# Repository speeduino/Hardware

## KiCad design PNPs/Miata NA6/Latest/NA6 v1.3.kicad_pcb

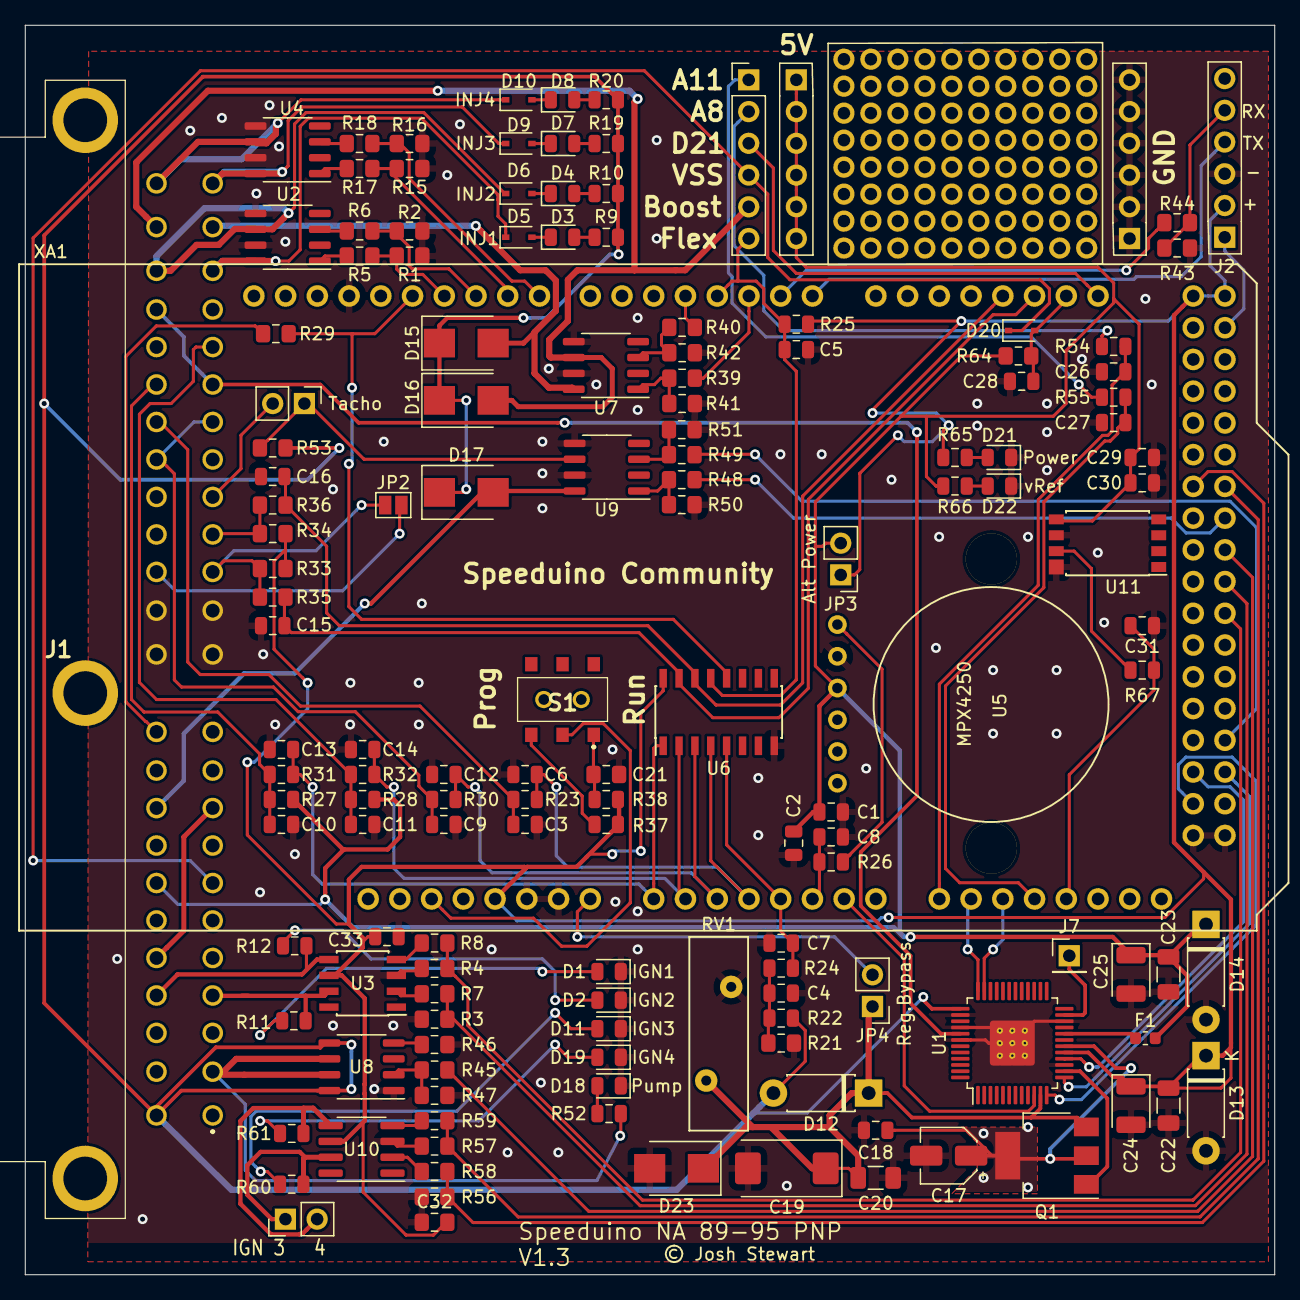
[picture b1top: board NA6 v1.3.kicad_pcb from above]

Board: 2 copper layers, 100.0 x 100.0 mm, 146 parts (0 on the bottom side), 110 nets.

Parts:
C1, C29: 0.01uF; C_0805_2012Metric
C2, C18, C30: 1uF; C_0805_2012Metric
C3, C4, C9, C10, C11, C15, C16, C26, C27, C28, C31, C33: 0.1uF; C_0805_2012Metric
C5: 0.27uF; C_0805_2012Metric
C6, C7, C12, C13, C14: 0.22uF; C_0805_2012Metric
C8: 470pf; C_0805_2012Metric
C17: 22uF; CP_Elec_4x5.8
C19: 10uF; CP_EIA-7343-31_Kemet-D
C20, C22, C23: 0.1uF; C_1206_3216Metric
C21: 22uF; C_0805_2012Metric_Pad1.15x1.40mm_HandSolder
C24, C25: 47uF; CP_EIA-3528-21_Kemet-B
C32: 0.1uF; C_0805_2012Metric_Pad1.15x1.40mm_HandSolder
D1, D2, D3, D4, D7, D8, D11, D18, D19: LED; LED_0805_2012Metric
D5, D6, D9, D10, D20: D; D_SOD-323
D12: D_Schottky; D_DO-41_SOD81_P7.62mm_Horizontal
D13, D14: D_Zener; D_DO-41_SOD81_P7.62mm_Horizontal
D15, D16, D17: D; D_SMB
D21, D22: LED_Green; LED_0805_2012Metric
D23: D_TVS; D_SMB
F1: Polyfuse; Fuse_0603_1608Metric
J1: 174917-1; 1749171
J2, J3, J4, J5: Conn_01x06; PinHeader_1x06_P2.54mm_Vertical
J6: Conn_01x02; PinHeader_1x02_P2.54mm_Vertical
J7: Conn_01x06; PinHeader_1x01_P2.54mm_Vertical
JP1: Jumper; PinHeader_1x02_P2.54mm_Vertical
JP2: Jumper; SolderJumper-2_P1.3mm_Open_Pad1.0x1.5mm
JP3, JP4: Jumper_2_Open; PinHeader_1x02_P2.54mm_Vertical
Q1: Q_PNP_BCEC; SOT-223-3_TabPin2
R1, R2, R3, R4, R15, R16, R41, R42, R47, R50, R51, R56, R57: 100k; R_0805_2012Metric_Pad1.15x1.40mm_HandSolder
R5, R6, R7, R8, R17, R18, R21, R29, R33, R34, R39, R40, R44, R45, R48, R49, R53, R58, R59, R64: 1k; R_0805_2012Metric_Pad1.15x1.40mm_HandSolder
R9, R10, R11, R12, R19, R20, R25, R60, R61: 2.4k; R_0805_2012Metric
R22: 3.9k; R_0805_2012Metric
R23, R24, R26, R30, R31, R32, R54, R55, R65, R66: 470R; R_0805_2012Metric
R27, R28, R52: 2.49k; R_0805_2012Metric
R35, R36: 220R; R_0805_2012Metric_Pad1.15x1.40mm_HandSolder
R37: 10k; R_0805_2012Metric
R38: 120R; R_0805_2012Metric
R43: 2k; R_0805_2012Metric_Pad1.15x1.40mm_HandSolder
R46: 10k; R_0805_2012Metric_Pad1.15x1.40mm_HandSolder
R67: 22K; R_0805_2012Metric
RV1: Varistor; RV_Disc_D15.5mm_W4.7mm_P7.5mm
S1: AYZ0202AGRLC
U1: MC33814; LQFP-48-1EP_7x7mm_P0.5mm_EP3.6x3.6mm_ThermalVias
U2, U4, U7, U9: VNLD5090; SO-8_3.9x4.9mm_P1.27mm
U3, U10: TC4424A; SOIC-8_3.9x4.9mm_P1.27mm
U5: MPX4250
U6: SP720; SOIC-16_3.9x9.9mm_P1.27mm
U8: VN5160S-E; SO-8_3.9x4.9mm_P1.27mm
U11: KP234
XA1: Arduino_Mega2560_Shield; Arduino_Mega2560_Shield_IO_Only

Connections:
12V-SW: D12.2, D15.1, D16.1, D17.1, J1.25, R9.2, R10.2, R19.2, R20.2, R22.2, R53.1, U1.37, U8.5, U8.8
33814-CSB: U1.10, XA1.A6
AC-Jump: J1.9, J1.29
ADC-Clamp-1: C13.1, R31.1, U6.1, XA1.A0
ADC-Clamp-2: C14.1, R32.1, U6.2, XA1.A1
ADC-Clamp-3: C12.1, R30.1, U6.3, XA1.A2
ADC-Clamp-4: C6.1, R23.1, U6.4, XA1.A3
ADC-Clamp-5: C7.1, R24.1, U6.5, XA1.A4
ADC-Clamp-11: R29.2, U6.12, XA1.D12
ADC-Clamp-12: C5.1, J5.6, R25.2, U6.13, XA1.D3
ADC-Clamp-13: C16.2, R36.1, U6.14, XA1.D18
ADC-Clamp-14: C15.2, R35.1, U6.15, XA1.D19
BOOST-OUT: D16.2, J1.47, J5.5, U7.6
CAM-IN: J1.15, R34.1, R36.2
CLT_Sensor: C11.1, J1.20, R28.1, R32.2
CRANK-IN: J1.14, JP2.1, R33.1, R35.2
Clutch_in: J1.35, R29.1
FAN-OUT: D17.2, J1.33, U9.8
GND: C1.1, C2.1, C3.2, C4.2, C5.2, C6.2, C7.2, C8.1, C9.2, C10.2, C11.2, C12.2, C13.2, C14.2, C15.1, C16.1, C17.2, C18.2, C19.2, C20.2, C21.2, C22.2, C23.2, C24.2, C25.2, C26.2, C27.2, C28.2, C29.1, C30.1, C31.1, C32.1, C33.1, D1.1, D2.1, D11.1, D13.2, D14.2, D18.1, D19.1, D21.1, D22.1, D23.2, J1.12, J1.13, J1.36, J1.37, J2.3, J4.1, J4.2, J4.3, J4.4, J4.5, J4.6, R1.2, R2.1, R3.2, R4.1, R15.2, R16.1, R21.1, R41.2, R42.1, R43.2, R46.2, R47.2, R50.2, R51.1, R56.2, R57.1, RV1.2, U1.15, U1.22, U1.38, U1.40, U1.42, U1.49, U2.5, U2.7, U3.3, U4.5, U4.7, U5.2, U6.8, U7.5, U7.7, U8.1, U9.5, U9.7, U10.3, U11.6, U11.8, XA1.GND1, XA1.GND2, XA1.GND3, XA1.GND5, XA1.GND6
IAT_Sensor: C10.1, J1.43, R27.1, R31.2
IDLE-OUT: D15.2, J1.23, U7.8
IGN-1-OUT: J1.4, R11.1, U3.7
IGN-2-OUT: J1.28, R12.1, U3.5
IGN-3-OUT: J6.1, R60.1, U10.7
IGN-4-OUT: J6.2, R61.1, U10.5
INJ-1-OUT: D5.1, J1.22, U2.8
INJ-2-OUT: D6.1, J1.46, U2.6
INJ-3-OUT: D9.1, J1.24, U4.8
INJ-4-OUT: D10.1, J1.48, U4.6
MCU-A5: C8.2, R26.1, XA1.A5
MCU-A8: C26.1, R54.2, XA1.A8
MCU-A9: U1.36, XA1.A9
MCU-A10: U1.35, XA1.A10
MCU-A11: C27.1, R55.1, XA1.A11
MCU-A12: C31.2, R67.2, XA1.A12
MCU-D0: J2.4, XA1.D0
MCU-D1: R44.1, XA1.D1
MCU-D2: R39.2, XA1.D2
MCU-D4: R40.2, XA1.D4
MCU-D8: R16.2, R18.2, XA1.D8
MCU-D9: R15.1, R17.2, XA1.D9
MCU-D10: R2.2, R6.2, XA1.D10
MCU-D11: R1.1, R5.2, XA1.D11
MCU-D20: C28.1, D20.2, R64.2, XA1.D20
MCU-D21: J5.3, XA1.D21
MCU-D23: J2.1, XA1.D23
MCU-D32: R56.1, R58.2, XA1.D32
MCU-D33: R57.2, R59.2, XA1.D33
MCU-D35: R48.2, XA1.D35
MCU-D37: R45.2, XA1.D37
MCU-D39: R3.1, R7.2, XA1.D39
MCU-D41: R4.2, R8.2, XA1.D41
MCU-D49: R49.2, XA1.D49
MCU-D50: U1.16, XA1.D50
MCU-D51: U1.13, XA1.D51
MCU-D52: U1.12, XA1.D52
unnamed: C4.1, R21.2, R22.1, R24.2
unnamed: C21.1, R38.1, S1.1
unnamed: D1.2, R11.2
unnamed: D2.2, R12.2
unnamed: D3.1, D5.2
unnamed: D3.2, R9.1
unnamed: D4.1, D6.2
unnamed: D4.2, R10.1
unnamed: D7.1, D9.2
unnamed: D7.2, R19.1
unnamed: D8.2, R20.1
unnamed: D8.1, D10.2
unnamed: D11.2, R60.2
unnamed: D18.2, R52.2
unnamed: D19.2, R61.2
unnamed: D21.2, R65.1
unnamed: D22.2, R66.1
unnamed: F1.1, U1.20
unnamed: J1.38, JP2.2
unnamed: J2.5, R43.1, R44.2
unnamed: J5.1, R55.2
unnamed: J5.2, R54.1
unnamed: JP1.1, R53.2, U9.6
unnamed: R5.1, U2.1
unnamed: R6.1, U2.3
unnamed: R7.1, U3.2
unnamed: R8.1, U3.4
unnamed: R17.1, U4.1
unnamed: R18.1, U4.3
unnamed: R26.2, U5.1
unnamed: R37.1, S1.3
unnamed: R39.1, R41.1, U7.1
unnamed: R40.1, R42.2, U7.3
unnamed: R45.1, R47.1, U8.2
unnamed: R46.1, U8.4
unnamed: R48.1, R50.1, U9.1
unnamed: R49.1, R51.2, U9.3
unnamed: R58.1, U10.2
unnamed: R59.1, U10.4
unnamed: R67.1, U11.7
O2_Sensor: C3.1, J1.42, R23.2
RESET: S1.2, XA1.RST1
ROUT1: J1.19, J1.45, U1.41
ROUT2: J7.1, U1.23
ST_Sig: J1.2, R52.1, U8.6, U8.7
TACHO-OUT: J1.16, JP1.2
TPS_Sensor: C9.1, J1.18, J1.41, R30.2
VDD: C22.1, C24.1, C32.2, C33.2, D13.1, J2.2, JP3.1, R25.1, R33.2, R34.2, R37.2, R38.2, R65.2, U1.17, U3.6, U6.16, U10.6, XA1.5V1, XA1.5V3, XA1.5V4
VDDA: C1.2, C2.2, C23.1, C25.1, C29.2, C30.2, D14.1, F1.2, J1.31, J3.1, J3.2, J3.3, J3.4, J3.5, J3.6, JP3.2, R27.2, R28.2, R64.1, R66.2, U5.3, U11.5
VIN: JP4.2, XA1.VIN
VPPREF: Q1.1, U1.14
VPPSENS: C17.1, C18.1, Q1.2, U1.18
VRegIn: C19.1, C20.1, D12.1, D23.1, JP4.1, Q1.3, RV1.1, U1.11
VSS: D20.1, J1.7, J5.4

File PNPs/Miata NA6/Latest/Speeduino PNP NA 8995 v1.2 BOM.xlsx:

Reference | Quantity | Value | Footprint | Manufacturer_Name | Manufacturer_Part_Number | URL | Digikey Part Number | Comment
C1 | 1 | 0.01uF | Capacitor_SMD:C_0805_2012Metric | Yageo | CC0805KRX7R9BB103 | https://www.digikey.com/product-detail/en/yageo/CC0805KRX7R9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 | 311-1136-1-ND
C17 | 1 | 22uF | Capacitor_SMD:CP_Elec_4x5.8 | Panasonic | EEE-FK0J220R | https://www.digikey.com/product-detail/en/panasonic-electron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 | PCE3765CT-ND
C19 | 1 | 10uF | Capacitor_Tantalum_SMD:CP_EIA-7343-31_Kemet-D | Kemet | T491D106K050AT | https://www.digikey.com/product-detail/en/kemet/T491D106K050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 | 399-8361-1-ND
C2 | 1 | 1uF | Capacitor_SMD:C_0805_2012Metric | Yageo | CC0805KKX7R7BB105 | https://www.digikey.com/product-detail/en/yageo/CC0805KKX7R7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 | 311-1365-1-ND
C20 C22 C23 | 3 | 0.1uF | Capacitor_SMD:C_1206_3216Metric | Kemet | C1206C104K5RAC7867 | https://www.digikey.com/product-detail/en/kemet/C1206C104K5R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 | 399-1249-1-ND
C21 | 1 | 22uF | Capacitor_SMD:C_0805_2012Metric_Pad1.15x1.40mm_HandSolder | Samsung | CL21A226KQCLRNC | https://www.digikey.com.au/product-detail/en/samsung-electro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 | 1276-6687-1-ND
C24 C25 | 2 | 47uF | Capacitor_Tantalum_SMD:CP_EIA-3528-21_Kemet-B | AVX | TAJB476K006RNJ | https://www.digikey.com/product-detail/en/avx-corporation/TA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 | 478-1692-1-ND
C3 C9 C10 C11 C4 C15 C16 C18 C27 C26 C28 | 11 | 0.1uF | Capacitor_SMD:C_0805_2012Metric | Yageo | CC0805KRX7R9BB104 | https://www.digikey.com.au/product-detail/en/yageo/CC0805KRX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 | 311-1140-1-ND
C5 | 1 | 0.27uF | Capacitor_SMD:C_0805_2012Metric | Yageo | CC0805JRX7R7BB274 | https://www.digikey.com.au/product-detail/en/yageo/CC0805JRX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 | 311-4268-1-ND
C6 C12 C13 C14 C7 | 5 | 0.22uF | Capacitor_SMD:C_0805_2012Metric | Samsung | CL21B224KOCNNNC | https://www.digikey.com/product-detail/en/samsung-electro-me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 | 1276-1284-1-ND
C8 | 1 | 470pf | Capacitor_SMD:C_0805_2012Metric | Yageo | CC0805KRX7R9BB471 | https://www.digikey.com/product-detail/en/yageo/CC0805KRX7R9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 | 311-1124-1-ND
D10 D9 D5 D6 D16 D15 D17 D20 | 8 | D | Diode_SMD:D_SOD-323 | Micro Commercial Co | 1N4448WX-TP | https://www.digikey.com/product-detail/en/micro-commercial-c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 | 1N4448WXTPMSCT-ND
D12 | 1 | D_Schottky | Diode_THT:D_DO-41_SOD81_P7.62mm_Horizontal | Micro Commercial Co | 1N5818-TP | https://www.digikey.com/product-detail/en/micro-commercial-c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 | 1N5818-TPCT-ND
D22 D21 | 2 | LED_Green | LED_SMD:LED_0805_2012Metric | Osram | LG R971-KN-1 | https://www.digikey.com/product-detail/en/osram-opto-semicon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 | 475-1410-1-ND
D4 D3 D8 D7 D1 D2 D11 D19 D18 | 9 | LED | LED_SMD:LED_0805_2012Metric | Osram | LH R974-LP-1 | https://www.digikey.com/product-detail/en/osram-opto-semicon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 | 475-1415-1-ND
F1 | 1 | Polyfuse | Fuse:Fuse_0603_1608Metric | Bel Fuse | 0ZCM0008FF2G | https://www.digikey.com.au/product-detail/en/bel-fuse-inc/0Z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 | 507-1817-1-ND
J1 | 1 | 174917-1 | Connector_Automotive:1749171 | TE Connectivity | 174917-1 | https://au.rs-online.com/web/p/pcb-connector-housings/720100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
Q1 | 1 | Q_PNP_BCEC | Package_TO_SOT_SMD:SOT-223-3_TabPin2 | Diodes Inc | FZT753TA | https://www.digikey.com.au/product-detail/en/diodes-incorpor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 | FZT753CT-ND
R1 R2 R15 R16 R3 R4 R56 R57 R42 R41 R51 R50 R47 | 13 | 100k | Resistor_SMD:R_0805_2012Metric_Pad1.15x1.40mm_HandSolder | Yageo | RC0805FR-07100KL | https://www.digikey.com/product-detail/en/yageo/RC0805FR-071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 | 311-100KCRCT-ND
R10 R9 R20 R19 R11 R12 R60 R61 R25 | 9 | 2.4k | Resistor_SMD:R_0805_2012Metric | Yageo | RC0805FR-072K4L | https://www.digikey.com/product-detail/en/yageo/RC0805FR-072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 | 311-2.40KCRCT-ND
R13 R14 R62 R63 | 4 | 10R | Resistor_SMD:R_0805_2012Metric | Yageo | RC0805FR-0710RL | https://www.digikey.com/product-detail/en/yageo/RC0805FR-071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 | 311-10.0CRCT-ND
R22 | 1 | 3.9k | Resistor_SMD:R_0805_2012Metric | Yageo | RC0805FR-073K9L | https://www.digikey.com/product-detail/en/yageo/RC0805FR-073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 | 311-3.90KCRCT-ND
R26 R23 R30 R31 R32 R24 R66 R65 R55 R54 R65 R66 | 12 | 470R | Resistor_SMD:R_0805_2012Metric | Panasonic | ERJ-6ENF4700V | https://www.digikey.com/product-detail/en/panasonic-electron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 | P470CCT-ND
R27 R28 R52 | 3 | 2.49k | Resistor_SMD:R_0805_2012Metric | Yageo | RT0805BRD072K49L | https://www.digikey.com/product-detail/en/yageo/RT0805BRD072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 | YAG1854CT-ND
R35 R36 | 2 | 220R | Resistor_SMD:R_0805_2012Metric_Pad1.15x1.40mm_HandSolder | Yageo | RC0805FR-07220RL | https://www.digikey.com/product-detail/en/yageo/RC0805FR-072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 | 311-220CRCT-ND
R37 R46 | 2 | 10k | Resistor_SMD:R_0805_2012Metric | Yageo | RC0805JR-0710KL | https://www.digikey.com/product-detail/en/yageo/RC0805JR-071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 | 311-10KARCT-ND
R38 | 1 | 120R | Resistor_SMD:R_0805_2012Metric | Yageo | RC0805FR-07120RL | https://www.digikey.com/product-detail/en/yageo/RC0805FR-071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 | 311-120CRCT-ND
R43 | 1 | 2k | Resistor_SMD:R_0805_2012Metric_Pad1.15x1.40mm_HandSolder | Yageo | RC0805FR-072KL | https://www.digikey.com/product-detail/en/yageo/RC0805FR-072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 | 311-2.00KCRCT-ND
R5 R6 R17 R18 R7 R8 R58 R59 R21 R29 R33 R34 R39 R40 R48 R49 R44 R45 R53 R64 | 20 | 1k | Resistor_SMD:R_0805_2012Metric_Pad1.15x1.40mm_HandSolder | Yageo | RC0805FR-071KL | https://www.digikey.com/product-detail/en/yageo/RC0805FR-071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 | 311-1.00KCRCT-ND
RV1 | 1 | Varistor | Varistor:RV_Disc_D15.5mm_W4.7mm_P7.5mm | Bourns Inc | MOV-14D220K | https://www.digikey.com.au/product-detail/en/bourns-inc/MOV-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 | MOV-14D220K-ND
S1 | 1 | AYZ0202AGRLC | AYZ0202AGRLC | C & K COMPONENTS | AYZ0202AGRLC | https://www.digikey.com.au/product-detail/en/c-k/AYZ0202AGRL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 | 401-2013-1-ND
U1 | 1 | MC33814 | Package_QFP:LQFP-48-1EP_7x7mm_P0.5mm_EP3.6x3.6mm_ThermalVias | NCP | MC33814 | http://au.element14.com/nxp/mc33814ae/ic-control-1-cylinder-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
U2 U4 U7 U9 | 4 | VNLD5090 | Package_SO:SO-8_3.9x4.9mm_P1.27mm | STMicro | VNLD5090-E | https://mouser.com/search/ProductDetail.aspx?R=0virtualkey0v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 | 497-18682-ND
U3 U10 | 2 | TC4424A | Package_SO:SOIC-8_3.9x4.9mm_P1.27mm | Microchip | TC4424AVOA | https://www.digikey.com/product-detail/en/microchip-technolo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 | TC4424AVOA-ND
U5 | 1 | MPX4250 | Misc:MPX4250 | NXP | MPX4250AP | https://www.digikey.com.au/product-detail/en/nxp-usa-inc/MPX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 | MPX4250AP-ND
U6 | 1 | SP720 | Package_SO:SOIC-16_3.9x9.9mm_P1.27mm | Littelfuse | SP720ABTG | https://www.digikey.com/product-detail/en/littelfuse-inc/SP7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 | F3162CT-ND
U8 | 1 | VN5160S-E | Package_SO:SO-8_3.9x4.9mm_P1.27mm | STMicro | VN5160S-E | https://www.digikey.com.au/products/en?keywords=VN5160S-E | 497-19720-ND
XA1 | 4 | Arduino_Mega2560 header pins | CONN HEADER .100" SNGL STR 40POS | Sullins Connector Solutions | PREC040SAAN-RC | https://www.digikey.com.au/products/en?keywords=S1012EC-40-ND |  | Pins attach to bottom of board

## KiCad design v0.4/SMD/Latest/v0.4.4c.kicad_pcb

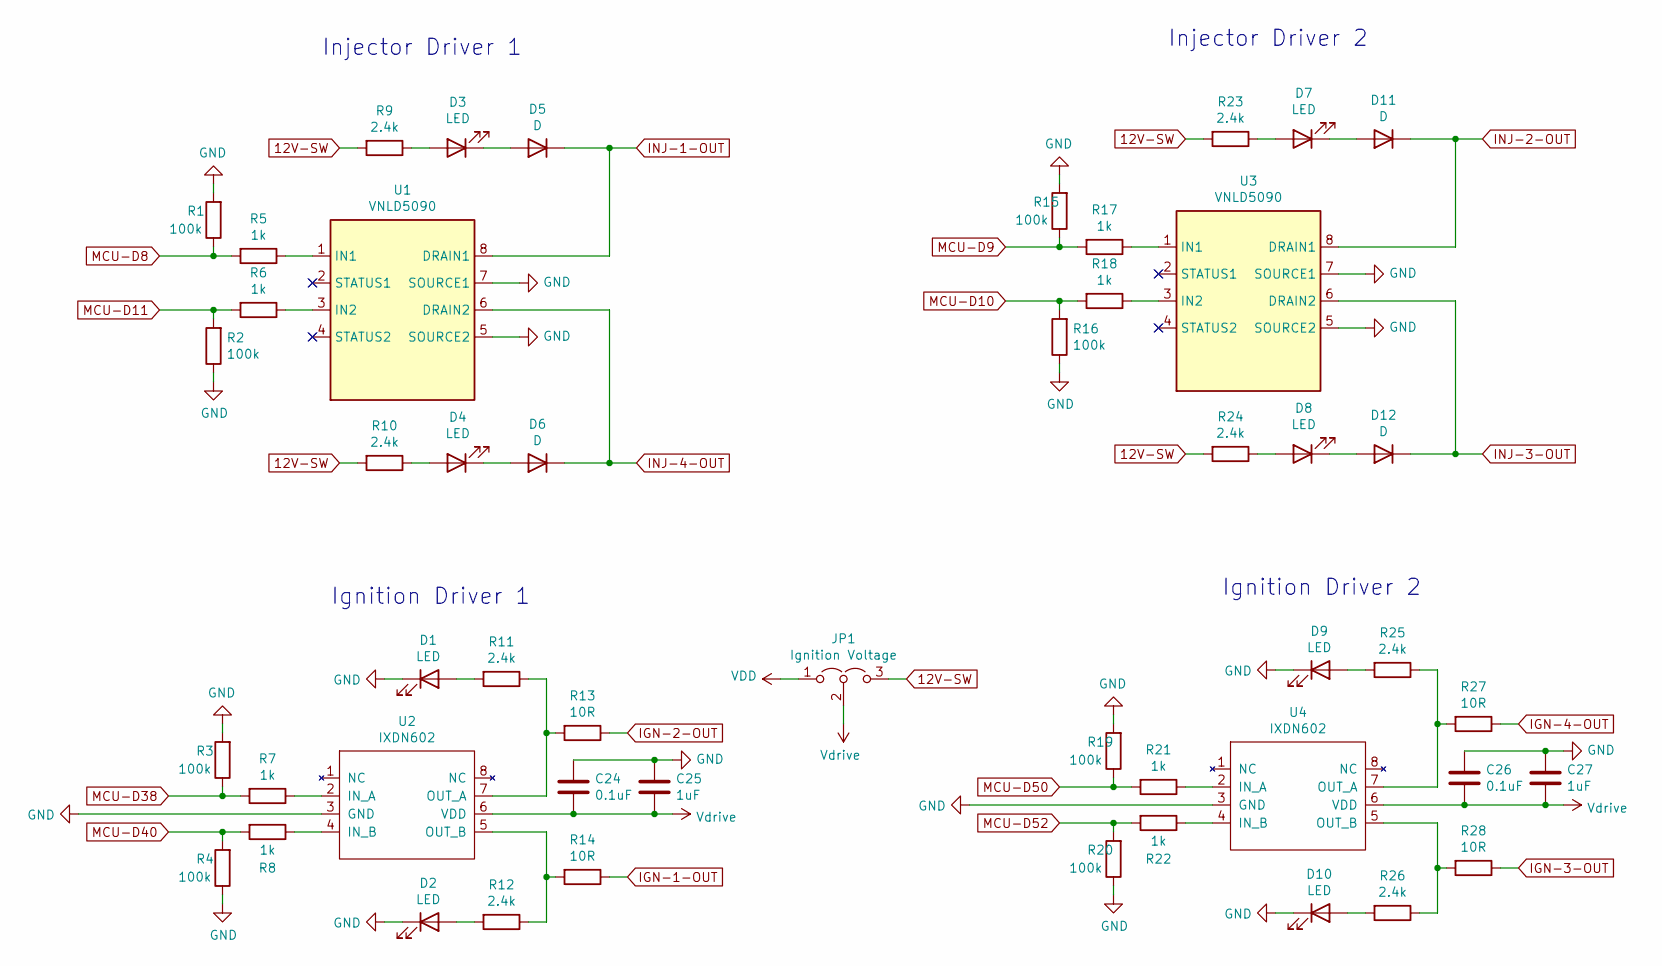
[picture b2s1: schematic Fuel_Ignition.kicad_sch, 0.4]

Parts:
C24, C26: 0.1uF; C_0805_2012Metric; Manufacturer_Part_Number CC0805KRX7R9BB104; Digikey Part Number 311-1140-1-ND
C25, C27: 1uF; C_0805_2012Metric; Manufacturer_Part_Number CC0805KKX7R7BB105; Digikey Part Number 311-1365-1-ND
D1, D2, D3, D4, D7, D8, D9, D10: LED; LED_0805_2012Metric; Manufacturer_Part_Number LH R974-LP-1; Digikey Part Number 475-1415-1-ND
D5, D6, D11, D12: D; D_SOD-323; Manufacturer_Part_Number 1N4448WX-TP; Digikey Part Number 1N4448WXTPMSCT-ND
JP1: Ignition Voltage; PinHeader_1x03_P2.54mm_Vertical; Manufacturer_Part_Number M20-9990345; Digikey Part Number 952-2263-ND
R1, R2, R3, R4, R15, R16, R19, R20: 100k; R_0805_2012Metric; Manufacturer_Part_Number RC0805FR-07100KL; Digikey Part Number 311-100KCRCT-ND
R5, R6, R7, R8, R17, R18, R21, R22: 1k; R_0805_2012Metric; Manufacturer_Part_Number RC0805FR-071KL; Digikey Part Number 311-1.00KCRCT-ND
R9, R10, R11, R12, R23, R24, R25, R26: 2.4k; R_0805_2012Metric; Manufacturer_Part_Number RC0805FR-072K4L; Digikey Part Number 311-2.40KCRCT-ND
R13, R14, R27, R28: 10R; R_1206_3216Metric; Manufacturer_Part_Number RC1206FR-0710RL; Digikey Part Number 311-10.0FRCT-ND
U1, U3: VNLD5090; SO-8_3.9x4.9mm_P1.27mm; Manufacturer_Part_Number VNLD5090-E; Digikey Part Number 497-18682-ND
U2, U4: IXDN602; SOIC-8_3.9x4.9mm_P1.27mm; Manufacturer_Part_Number IXDN602SIATR; Digikey Part Number 212-IXDN602SIACT-ND

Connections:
GND: C24.1, C25.1, C26.1, C27.1, D1.1 (K), D2.1 (K), D9.1 (K), D10.1 (K), R1.2, R2.1, R3.2, R4.1, R15.2, R16.1, R19.2, R20.1, U1.5 (SOURCE2), U1.7 (SOURCE1), U2.3 (GND), U3.5 (SOURCE2), U3.7 (SOURCE1), U4.3 (GND); also elsewhere on the board
IGN-1-OUT: R14.1; also elsewhere on the board
IGN-2-OUT: R13.1; also elsewhere on the board
IGN-3-OUT: R28.1; also elsewhere on the board
IGN-4-OUT: R27.1; also elsewhere on the board
INJ-1-OUT: D5.1 (K), U1.8 (DRAIN1); also elsewhere on the board
INJ-2-OUT: D11.1 (K), U3.8 (DRAIN1); also elsewhere on the board
INJ-3-OUT: D12.1 (K), U3.6 (DRAIN2); also elsewhere on the board
INJ-4-OUT: D6.1 (K), U1.6 (DRAIN2); also elsewhere on the board
MCU-D8: R1.1, R5.2; also elsewhere on the board
MCU-D9: R15.1, R17.2; also elsewhere on the board
MCU-D10: R16.2, R18.2; also elsewhere on the board
MCU-D11: R2.2, R6.2; also elsewhere on the board
MCU-D38: R3.1, R7.2; also elsewhere on the board
MCU-D40: R4.2, R8.2; also elsewhere on the board
MCU-D50: R19.1, R21.2; also elsewhere on the board
MCU-D52: R20.2, R22.2; also elsewhere on the board
unnamed: D1.2 (A), R11.2
unnamed: D2.2 (A), R12.2
unnamed: D3.1 (K), D5.2 (A)
unnamed: D3.2 (A), R9.1
unnamed: D4.1 (K), D6.2 (A)
unnamed: D4.2 (A), R10.1
unnamed: D7.2 (A), R23.1
unnamed: D8.2 (A), R24.1
unnamed: D9.2 (A), R25.2
unnamed: D10.2 (A), R26.2
unnamed: D7.1 (K), D11.2 (A)
unnamed: D8.1 (K), D12.2 (A)
unnamed: R5.1, U1.1 (IN1)
unnamed: R6.1, U1.3 (IN2)
unnamed: R7.1, U2.2 (IN_A)
unnamed: R8.1, U2.4 (IN_B)
unnamed: R11.1, R13.2, U2.7 (OUT_A)
unnamed: R12.1, R14.2, U2.5 (OUT_B)
unnamed: R17.1, U3.1 (IN1)
unnamed: R18.1, U3.3 (IN2)
unnamed: R21.1, U4.2 (IN_A)
unnamed: R22.1, U4.4 (IN_B)
unnamed: R25.1, R27.2, U4.7 (OUT_A)
unnamed: R26.1, R28.2, U4.5 (OUT_B)
Vdrive: C24.2, C25.2, C26.2, C27.2, JP1.2 (C), U2.6 (VDD), U4.6 (VDD)

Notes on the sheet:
Injector Driver 2
Ignition Driver 2
Injector Driver 1
Ignition Driver 1

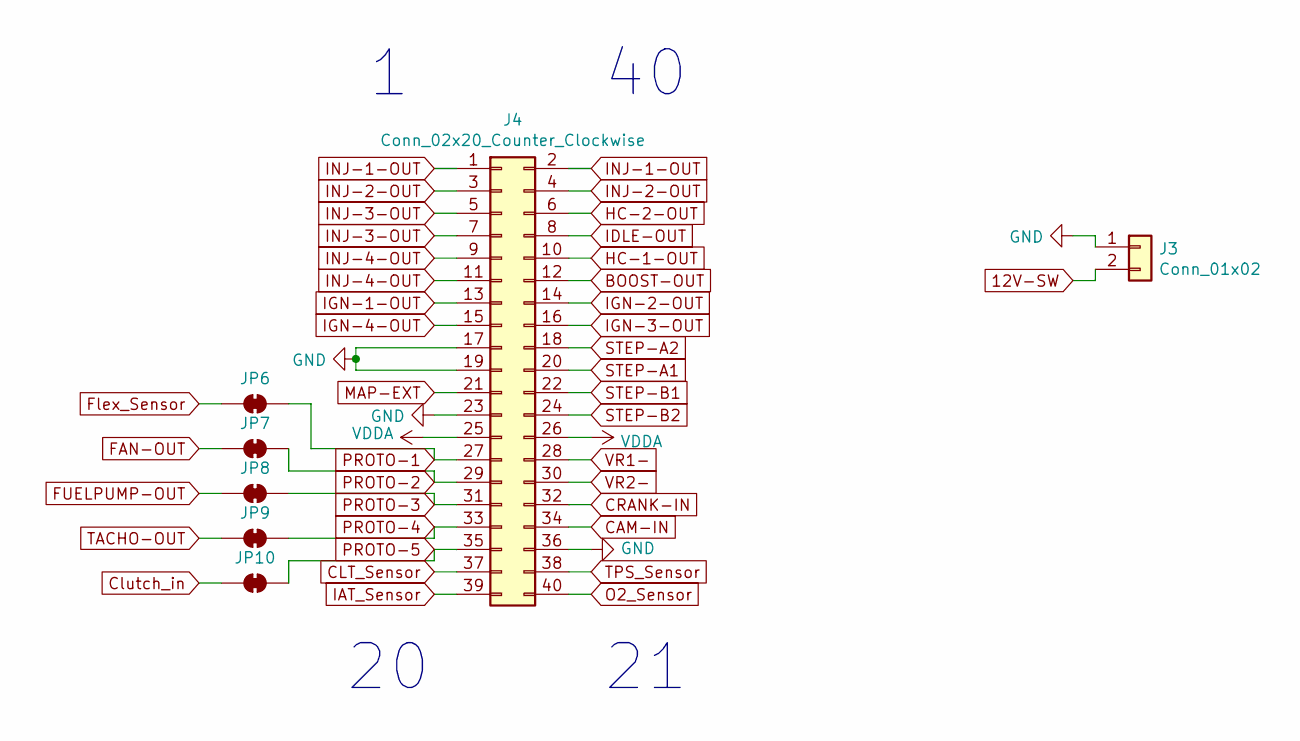
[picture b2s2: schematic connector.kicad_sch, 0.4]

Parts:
J3: Conn_01x02; TerminalBlock_Phoenix_PT-1,5-2-5.0-H_1x02_P5.00mm_Horizontal
J4: Conn_02x20_Counter_Clockwise; IDC-Header_2x20_P2.54mm_Vertical
JP6, JP7, JP8, JP9, JP10: SolderJumper_2_Bridged; SolderJumper-2_P1.3mm_Bridged_Pad1.0x1.5mm

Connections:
ADC-Clamp-10: JP6.1 (A); also elsewhere on the board
BOOST-OUT: J4.12; also elsewhere on the board
CAM-IN: J4.34; also elsewhere on the board
CLT_Sensor: J4.37; also elsewhere on the board
CRANK-IN: J4.32; also elsewhere on the board
Clutch_in: JP10.1 (A); also elsewhere on the board
FAN-OUT: JP7.1 (A); also elsewhere on the board
FUELPUMP-OUT: JP8.1 (A); also elsewhere on the board
GND: J3.1, J4.17, J4.19, J4.23, J4.36; also elsewhere on the board
HC-1-OUT: J4.10; also elsewhere on the board
HC-2-OUT: J4.6; also elsewhere on the board
IAT_Sensor: J4.39; also elsewhere on the board
IDLE-OUT: J4.8; also elsewhere on the board
IGN-1-OUT: J4.13; also elsewhere on the board
IGN-2-OUT: J4.14; also elsewhere on the board
IGN-3-OUT: J4.16; also elsewhere on the board
IGN-4-OUT: J4.15; also elsewhere on the board
INJ-1-OUT: J4.1, J4.2; also elsewhere on the board
INJ-2-OUT: J4.3, J4.4; also elsewhere on the board
INJ-3-OUT: J4.5, J4.7; also elsewhere on the board
INJ-4-OUT: J4.9, J4.11; also elsewhere on the board
MAP-EXT: J4.21; also elsewhere on the board
O2_Sensor: J4.40; also elsewhere on the board
PROTO-1: J4.27, JP6.2 (B); also elsewhere on the board
PROTO-2: J4.29, JP7.2 (B); also elsewhere on the board
PROTO-3: J4.31, JP8.2 (B); also elsewhere on the board
PROTO-4: J4.33, JP9.2 (B); also elsewhere on the board
PROTO-5: J4.35, JP10.2 (B); also elsewhere on the board
STEP-A1: J4.20; also elsewhere on the board
STEP-A2: J4.18; also elsewhere on the board
STEP-B1: J4.22; also elsewhere on the board
STEP-B2: J4.24; also elsewhere on the board
TACHO-OUT: JP9.1 (A); also elsewhere on the board
TPS_Sensor: J4.38; also elsewhere on the board
VDDA: J4.25, J4.26; also elsewhere on the board
VR1-: J4.28; also elsewhere on the board
VR2-: J4.30; also elsewhere on the board

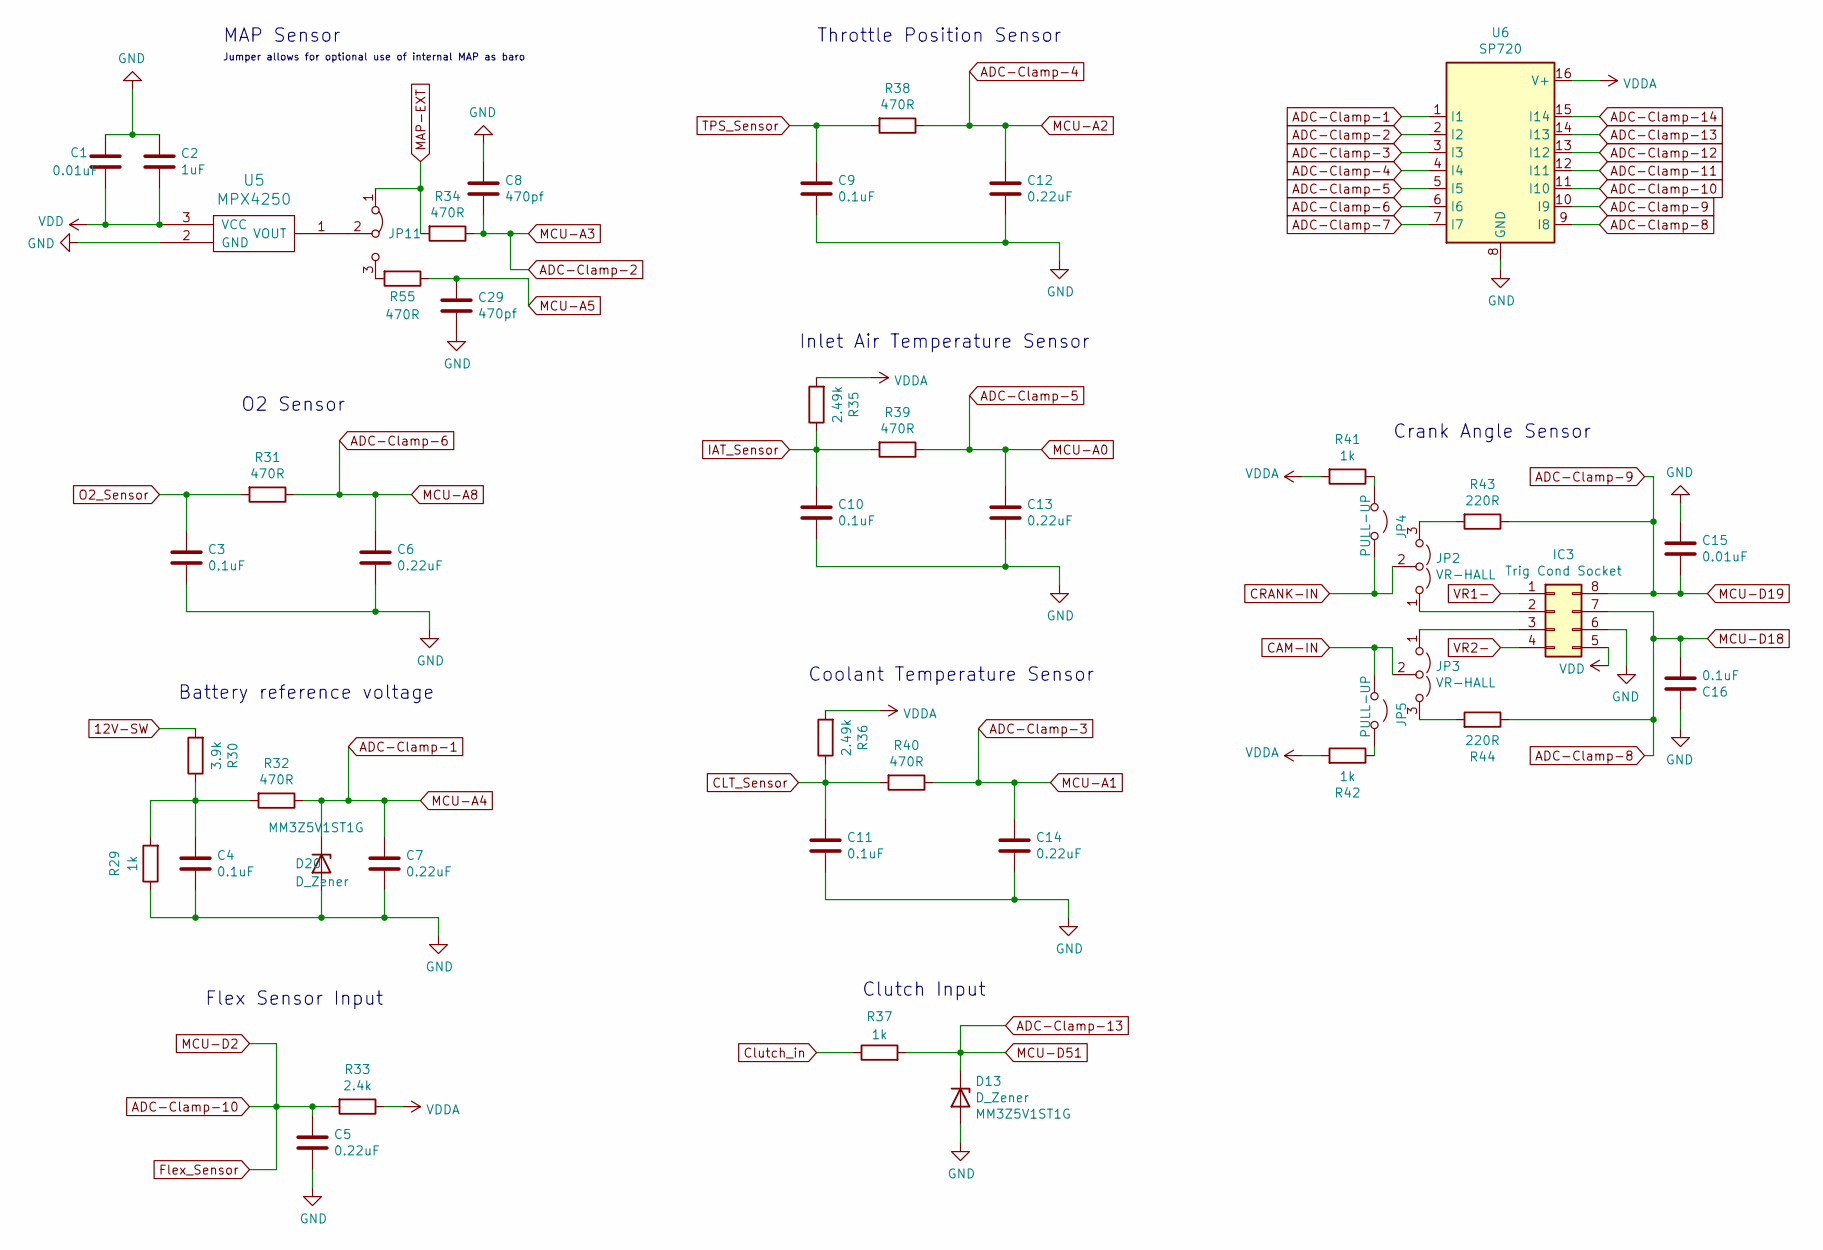
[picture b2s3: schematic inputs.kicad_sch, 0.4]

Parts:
C1, C15: 0.01uF; C_0805_2012Metric; Manufacturer_Part_Number CC0805KRX7R9BB103; Digikey Part Number 311-1136-1-ND
C2: 1uF; C_0805_2012Metric; Manufacturer_Part_Number CC0805KKX7R7BB105; Digikey Part Number 311-1365-1-ND
C3, C4, C9, C10, C11, C16: 0.1uF; C_0805_2012Metric; Manufacturer_Part_Number CC0805KRX7R9BB104; Digikey Part Number 311-1140-1-ND
C5, C6, C7, C12, C13, C14: 0.22uF; C_0805_2012Metric; Manufacturer_Part_Number CL21B224KOCNNNC; Digikey Part Number 1276-1284-1-ND
C8, C29: 470pf; C_0805_2012Metric; Manufacturer_Part_Number CC0805KRX7R9BB471; Digikey Part Number 311-1124-1-ND
D13, D20: D_Zener; D_SOD-323; Part # MM3Z5V1ST1G; Digikey Part Number MM3Z5V1ST1GOSCT-ND
IC3: Trig Cond Socket; DIP-8_W7.62mm_Socket
JP2, JP3: VR-HALL; PinHeader_1x03_P2.54mm_Vertical; Manufacturer_Part_Number M20-9990345; Digikey Part Number 952-2263-ND
JP4, JP5: PULL-UP; PinHeader_1x02_P2.54mm_Vertical; Manufacturer_Part_Number M20-9990245; Digikey Part Number 952-2261-ND
JP11: Jumper_3_Bridged12; SolderJumper-3_P1.3mm_Bridged12_RoundedPad1.0x1.5mm
R29, R37, R41, R42: 1k; R_0805_2012Metric; Manufacturer_Part_Number RC0805FR-071KL; Digikey Part Number 311-1.00KCRCT-ND
R30: 3.9k; R_0805_2012Metric; Manufacturer_Part_Number RC0805FR-073K9L; Digikey Part Number 311-3.90KCRCT-ND
R31, R32, R34, R38, R39, R40, R55: 470R; R_0805_2012Metric; Manufacturer_Part_Number ERJ-6ENF4700V; Digikey Part Number P470CCT-ND
R33: 2.4k; R_0805_2012Metric; Manufacturer_Part_Number RC0805FR-072K4L; Digikey Part Number 311-2.40KCRCT-ND
R35, R36: 2.49k; R_0805_2012Metric; Manufacturer_Part_Number RT0805BRD072K49L; Digikey Part Number YAG1854CT-ND
R43, R44: 220R; R_0805_2012Metric; Manufacturer_Part_Number RC0805FR-07220RL; Digikey Part Number 311-220CRCT-ND
U5: MPX4250; Manufacturer_Part_Number MPX4250AP; Digikey Part Number MPX4250AP-ND
U6: SP720; SOIC-16_3.9x9.9mm_P1.27mm; Manufacturer_Part_Number SP720ABTG; Digikey Part Number F3162CT-ND

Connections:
ADC-Clamp-1: C7.1, D20.1 (K), R32.1, U6.1 (I1); also elsewhere on the board
ADC-Clamp-2: C8.2, R34.1, U6.2 (I2); also elsewhere on the board
ADC-Clamp-3: C14.1, R40.1, U6.3 (I3); also elsewhere on the board
ADC-Clamp-4: C12.1, R38.1, U6.4 (I4); also elsewhere on the board
ADC-Clamp-5: C13.1, R39.1, U6.5 (I5); also elsewhere on the board
ADC-Clamp-6: C6.1, R31.1, U6.6 (I6); also elsewhere on the board
ADC-Clamp-7: U6.7 (I7)
ADC-Clamp-8: C16.2, IC3.7, R44.1, U6.9 (I8); also elsewhere on the board
ADC-Clamp-9: C15.2, IC3.8, R43.1, U6.10 (I9); also elsewhere on the board
ADC-Clamp-10: C5.1, R33.2, U6.11 (I10); also elsewhere on the board
ADC-Clamp-11: U6.12 (I11)
ADC-Clamp-12: U6.13 (I12)
ADC-Clamp-13: D13.1 (K), R37.2, U6.14 (I13); also elsewhere on the board
ADC-Clamp-14: U6.15 (I14)
CAM-IN: JP3.2 (C), JP5.1 (A); also elsewhere on the board
CLT_Sensor: C11.1, R36.1, R40.2; also elsewhere on the board
CRANK-IN: JP2.2 (C), JP4.1 (A); also elsewhere on the board
Clutch_in: R37.1; also elsewhere on the board
GND: C1.1, C2.1, C3.2, C4.2, C5.2, C6.2, C7.2, C8.1, C9.2, C10.2, C11.2, C12.2, C13.2, C14.2, C15.1, C16.1, C29.2, D13.2 (A), D20.2 (A), IC3.6, R29.1, U5.2 (GND), U6.8 (GND); also elsewhere on the board
IAT_Sensor: C10.1, R35.1, R39.2; also elsewhere on the board
MAP-EXT: JP11.1 (A), R34.2; also elsewhere on the board
MCU-A5: C29.1, R55.1; also elsewhere on the board
unnamed: C4.1, R29.2, R30.1, R32.2
unnamed: IC3.2, JP2.1 (A)
unnamed: IC3.3, JP3.1 (A)
unnamed: JP2.3 (B), R43.2
unnamed: JP3.3 (B), R44.2
unnamed: JP4.2 (B), R41.1
unnamed: JP5.2 (B), R42.1
unnamed: JP11.2 (C), U5.1 (VOUT)
unnamed: JP11.3 (B), R55.2
O2_Sensor: C3.1, R31.2; also elsewhere on the board
TPS_Sensor: C9.1, R38.2; also elsewhere on the board
VDDA: R33.1, R35.2, R36.2, R41.2, R42.2, U6.16 (V+); also elsewhere on the board
VR1-: IC3.1; also elsewhere on the board
VR2-: IC3.4; also elsewhere on the board

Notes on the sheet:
Jumper allows for optional use of internal MAP as baro
Crank Angle Sensor
Battery reference voltage
O2 Sensor
Inlet Air Temperature Sensor
Throttle Position Sensor
Flex Sensor Input
Clutch Input
MAP Sensor
Coolant Temperature Sensor

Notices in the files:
PNPs/Miata NA6/Latest/NA6 v1.3.kicad_pcb:
© Josh Stewart
